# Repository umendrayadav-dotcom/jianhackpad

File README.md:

# jIAN HACKPAD

A custom mechanical keyboard macropad featuring RGB backlighting and powered by the Seeed Studio XIAO RP2040 microcontroller.

## Overview

JIANHACKPAD is a 12-key mechanical keyboard PCB designed for custom macropad builds. The board features Cherry MX compatible switches, addressable RGB LEDs, and a compact form factor perfect for programmable shortcuts and macros.

## Features

- **12 Cherry MX Compatible Switches** - Standard PCB-mount mechanical switches
- **RGB Backlighting** - SK6812MINI addressable RGB LEDs for per-key lighting
- **XIAO RP2040 Microcontroller** - Powered by Seeed Studio's XIAO RP2040 module with RP2040 chip
- **4-Layer PCB Design** - Professional PCB layout with proper power and signal routing
- **Open Source Hardware** - Full KiCad design files included

## Project Structure

```
jianhackpad/
├── CAD/                    # 3D CAD models
│   └── jianhackpad.step   # 3D model in STEP format
├── Firmware/               # Firmware code (to be added)
├── PCB/                    # KiCad PCB design files
│   ├── jainhackpad-schematic.kicad_sch  # Schematic design
│   └── jianhackpad.kicad_pcb            # PCB layout
└── resources/              # Project resources
    ├── 3d-model.jpeg       # 3D model render
    ├── 3d-overview.jpeg    # 3D overview render
    └── pcb.png             # PCB render
```

## Hardware Specifications

### Components

- **Microcontroller**: Seeed Studio XIAO RP2040
  - RP2040 dual-core ARM Cortex-M0+ processor
  - USB-C connectivity
  - 14 GPIO pins
  
- **Switches**: Cherry MX compatible (12x)
  - PCB mount
  - 1.00u key spacing
  
- **LEDs**: SK6812MINI (12x)
  - Addressable RGB LEDs
  - Per-key lighting support
  - WS2812B compatible protocol

### PCB Details

- **Layers**: 4-layer board
- **Thickness**: 1.1962mm
- **Design Tool**: KiCad 9.0

## Bill of Materials (BOM)

| Qty | Reference | Component | Description | Notes |
|-----|-----------|-----------|-------------|-------|
| 1 | U1 | XIAO-RP2040-DIP | Seeed Studio XIAO RP2040 Module | RP2040 microcontroller with USB-C |
| 12 | SW1-SW12 | Cherry MX Switch | Mechanical keyboard switch | PCB mount, 1.00u spacing |
| 12 | D1-D12 | SK6812MINI | Addressable RGB LED | PLCC4, 3.5x3.5mm, WS2812B compatible |
| 1 | OL1 | OLED Display | SSD1306 OLED Display | 0.91" 128x32, I2C interface |
| 1 | - | PCB | Custom PCB | 4-layer, 1.1962mm thickness |
| 1 | - | USB-C Cable | USB-C to USB-A cable | For power and programming |

### Optional Components

- Keycaps (12x) - Cherry MX compatible keycaps
- Case/Enclosure - Custom case design (see CAD folder)
- Stabilizers - If using larger keycaps (2u or larger)

### Component Sources

- **XIAO RP2040**: [Seeed Studio](https://www.seeedstudio.com/XIAO-RP2040-v1-0-p-5026.html)
- **SK6812MINI LEDs**: Available from Adafruit, SparkFun, or AliExpress
- **Cherry MX Switches**: Available from various keyboard vendors (KBDfans, NovelKeys, etc.)
- **OLED Display**: Generic SSD1306 0.91" OLED modules available from various suppliers

## Getting Started

### Prerequisites

- KiCad 9.0 or later (for viewing/editing PCB files)
- Seeed Studio XIAO RP2040 module
- 12x Cherry MX compatible switches
- 12x SK6812MINI RGB LEDs
- USB-C cable
- Soldering equipment

### Firmware

Firmware code will be added to the `Firmware/` directory. The board is compatible with popular keyboard firmware frameworks such as:

- [QMK](https://qmk.fm/)
- [KMK](https://github.com/KMKfw/kmk_firmware)
- [ZMK](https://zmk.dev/)

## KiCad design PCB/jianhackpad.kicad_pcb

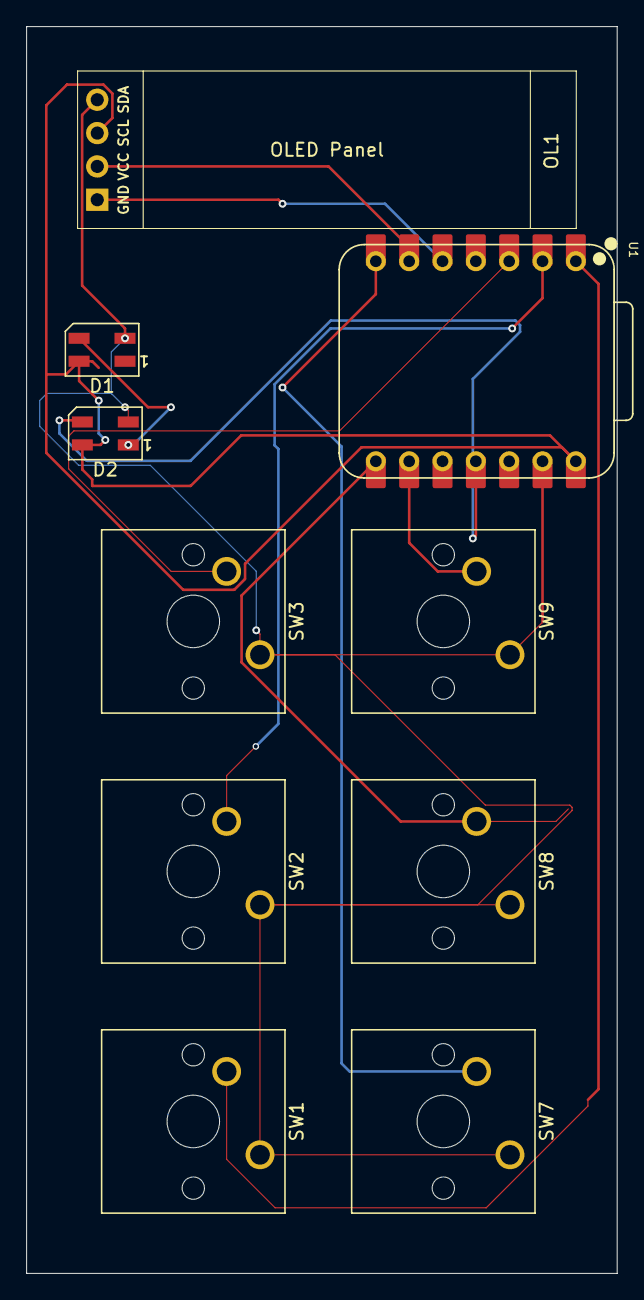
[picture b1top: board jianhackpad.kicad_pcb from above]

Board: 4 copper layers, 45.0 x 95.0 mm, 10 parts (0 on the bottom side), 12 nets.

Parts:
D1, D2: SK6812MINI; LED_SK6812MINI_PLCC4_3.5x3.5mm_P1.75mm
OL1: OLED; SSD1306-0.91-OLED-4pin-128x32
SW1, SW2, SW3, SW7, SW8, SW9: SW_Push; SW_Cherry_MX_1.00u_PCB
U1: XIAO-RP2040-DIP

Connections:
+5V: D1.4 (VDD), D2.4 (VDD), OL1.3 (VCC), U1.14 (VBUS)
GND: D1.2 (VSS), D2.2 (VSS), OL1.4 (GND), SW1.1, SW2.1, SW3.1, SW7.1, SW8.1, SW9.1, U1.13 (GND)
unnamed: D1.3 (DIN), D2.1 (DOUT)
unnamed: D2.3 (DIN), U1.11 (GPIO3/MOSI)
unnamed: OL1.2 (SCL), U1.6 (GPIO7/SCL)
unnamed: OL1.1 (SDA), U1.5 (GPIO6/SDA)
unnamed: SW7.2, U1.7 (GPIO0/TX)
unnamed: SW8.2, U1.8 (GPIO1/RX)
unnamed: SW9.2, U1.9 (GPIO2/SCK)
unnamed: SW1.2, U1.1 (GPIO26/ADC0/A0)
unnamed: SW2.2, U1.2 (GPIO27/ADC1/A1)
unnamed: SW3.2, U1.3 (GPIO28/ADC2/A2)

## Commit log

2025-12-29 add readme
